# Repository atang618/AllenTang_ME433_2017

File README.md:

Allen Tang
March 28, 2017

This repository contains the project work for ME 433 Advanced Mechatronics at Northwestern University.

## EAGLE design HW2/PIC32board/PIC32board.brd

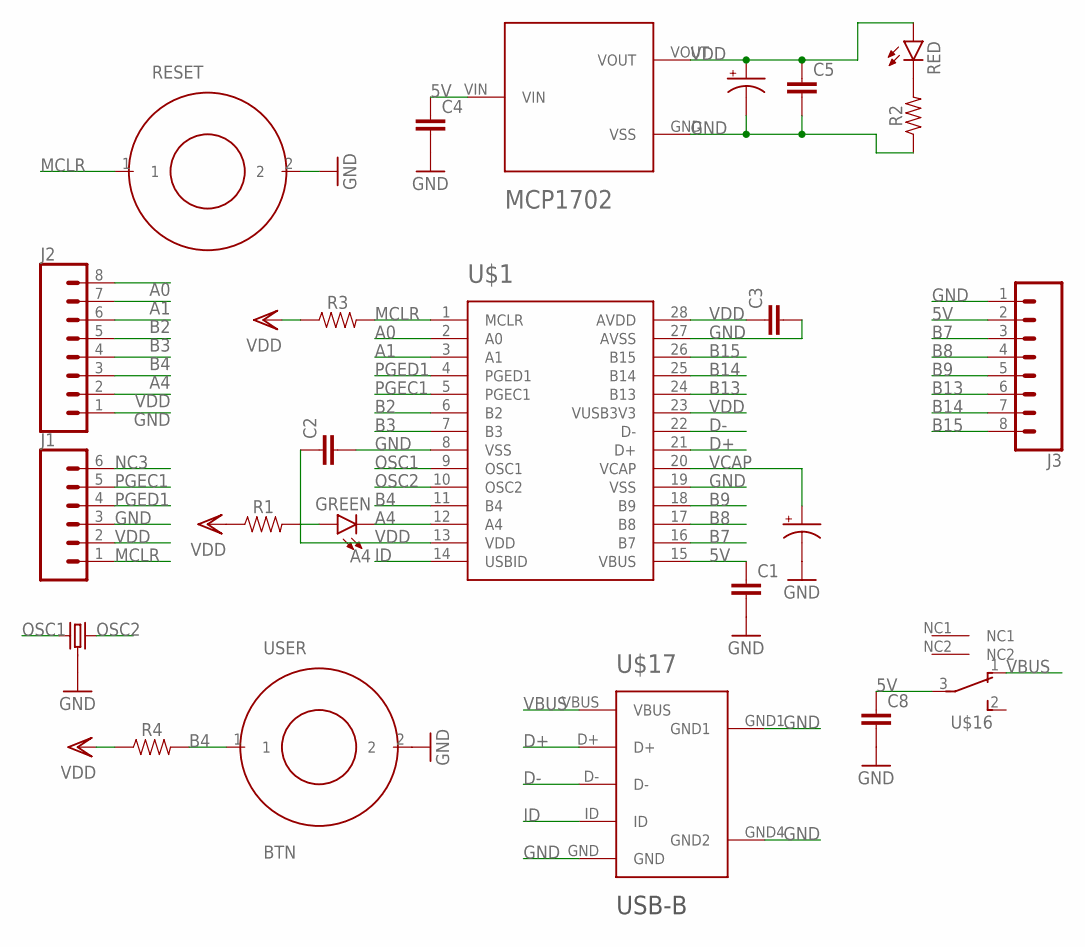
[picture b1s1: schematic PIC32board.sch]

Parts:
A4: GREEN; LED-0603
C1, C2, C3, C4, C5, C8: 0.1µF-SMD; 0603
C6, C7: 10µF-POL; 10µF_THROUGHHOLE
J1: CONN_06SILK_FEMALE_PTH; 1X06
J2, J3: CONN_08"; 1X08
PWR: RED; LED-0603
R1, R2: 330; 0603
R3, R4: 10KOHM-SMD; 0603
RESET: BTN
U$1: PIC32MX250F128B_SOCKET; DIP28
U$2: MCP1702; TO92
U$8: 8MHZ-CRYSTAL
U$16: SLIDE-SWITCH
U$17: USB-B; USB-MINIB-THM-MOLEX
USER: BTN

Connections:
5V: C1.1, C4.1, C8.1, J3.2, U$1.15 (VBUS), U$2.VIN, U$16.3
A0: J2.8, U$1.2 (A0)
A1: J2.7, U$1.3 (A1)
A4: A4.C, J2.3, U$1.12 (A4)
B2: J2.6, U$1.6 (B2)
B3: J2.5, U$1.7 (B3)
B4: J2.4, R4.2, U$1.11 (B4), USER.1
B7: J3.3, U$1.16 (B7)
B8: J3.4, U$1.17 (B8)
B9: J3.5, U$1.18 (B9)
B13: J3.6, U$1.24 (B13)
B14: J3.7, U$1.25 (B14)
B15: J3.8, U$1.26 (B15)
D+: U$1.21 (D+), U$17.D+
D-: U$1.22 (D-), U$17.D-
GND: C1.2, C2.2, C3.2, C4.2, C5.2, C6.NEG (-), C7.NEG (-), C8.2, J1.3, J2.1, J3.1, R2.1, RESET.2, U$1.8 (VSS), U$1.19 (VSS), U$1.27 (AVSS), U$2.GND (VSS), U$8.2 (VSS), U$17.GND, U$17.GND1, U$17.GND4 (GND2), USER.2
ID: U$1.14 (USBID), U$17.ID
MCLR: J1.1, R3.2, RESET.1, U$1.1 (MCLR)
unnamed: PWR.C, R2.2
unnamed: A4.A, R1.2
NC3: J1.6
OSC1: U$1.9 (OSC1), U$8.1
OSC2: U$1.10 (OSC2), U$8.3 (2)
PGEC1: J1.5, U$1.5 (PGEC1)
PGED1: J1.4, U$1.4 (PGED1)
VBUS: U$16.1, U$17.VBUS
VCAP: C7.POS (+), U$1.20 (VCAP)
VDD: C2.1, C3.1, C5.1, C6.POS (+), J1.2, J2.2, PWR.A, R1.1, R3.1, R4.1, U$1.13 (VDD), U$1.23 (VUSB3V3), U$1.28 (AVDD), U$2.VOUT

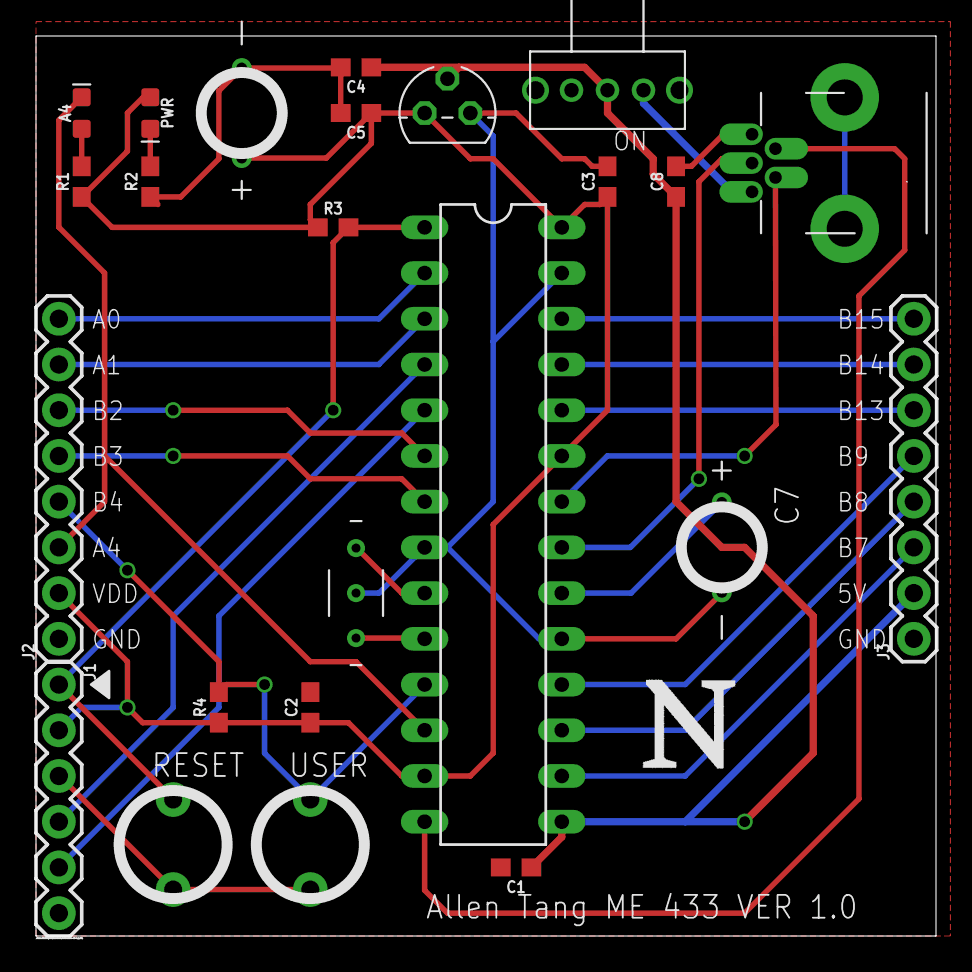
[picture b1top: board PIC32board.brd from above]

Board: 2 copper layers, 50.0 x 50.0 mm, 24 parts (0 on the bottom side), 27 nets.

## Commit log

2017-03-29 added pictures
2017-03-29 added some pragmas
2017-03-29 finished pragmas
2017-03-29 initialize LED
2017-03-29 added LED 1000Hz
2017-03-29 added pushbutton
2017-03-31 started schematic
2017-03-31 finished first draft of schematic
2017-04-03 added library
2017-04-04 started brd file
2017-04-05 finished adding traces
2017-04-05 completed PCB
2017-04-05 created gerber files
2017-04-05 changed to HW2-3
2017-04-05 removed old HW2
2017-04-07 wrote init function
2017-04-07 wrote setVoltage
2017-04-07 created makeSINE
2017-04-07 wrote makeTri
2017-04-07 wrote interrupt
2017-04-08 moved build init to main
2017-04-08 deleted config.c
2017-04-10 fixed ISR bug
2017-04-10 completed HW4
2017-04-10 updated SCK to 12 MHz
2017-04-10 added circuit diagram
2017-04-12 first draft of I2C code
2017-04-12 revised I2C code
2017-04-13 revised I2C
2017-04-13 updated setExpander
2017-04-13 finalized code
2017-04-13 added HW 6 and initial algorithm
2017-04-13 add drawString function
2017-04-13 fixed bug with drawString
2017-04-14 added drawBar
2017-04-14 Added timer
2017-04-14 changed timer frequency
2017-04-14 changed valid pixel boundaries
2017-04-17 revised flashing issue
2017-04-17 clear screen after reset
2017-04-18 added FPS reading
2017-04-18 wrote IMU init
2017-04-18 fixed FPS
2017-04-19 added i2c_multiple function and data format
2017-04-19 added screen drawing bars
2017-04-19 flipped direction of bars
2017-04-19 refresh bar on crossover
2017-04-22 added HW8 with LED blink
2017-04-22 uploaded LCD and IMU code
2017-04-25 added initial shell for HW9
2017-04-25 integrated IMU
2017-04-25 completed HW9
2017-05-01 updated PIC to send data to Matlab
2017-05-01 changed weights for the filters
2017-05-02 added basic shell for USB mouse
2017-05-02 removed new folder
2017-05-02 added IMU
2017-05-03 debugging and final IMU mouse
2017-05-05 added Hello World barebone
2017-05-05 added slider bar
2017-05-05 made progress bar start at 0
2017-05-10 added initial Android Camera
2017-05-10 changed starting point
2017-05-12 initial PIC and Android shell for HW14
2017-05-12 added pic to Android functions
2017-05-12 stylistic changes
2017-05-17 added a picture of the 3 sided box CAD
2017-05-17 pictures of laser cut box
2017-05-19 updated images
2017-05-26 started final Android and CDC code
2017-05-31 updated Android code
2017-05-31 deleted timer interrupt
2017-05-31 added USB capabilities
2017-05-31 added scroll view
2017-05-31 added androidUSB interface on MCU
2017-05-31 got OC to work
2017-05-31 fixed issue with android app
2017-06-04 changed OC1 to max speed
2017-06-05 added servo code
2017-06-05 turn off blue flag
2017-06-06 separate code for just motor control
2017-06-06 added HW18 code
2017-06-06 tweaked HW18 code
2017-06-06 changed final Pic code
2017-06-06 upped gain on Android
2017-06-09 final code
